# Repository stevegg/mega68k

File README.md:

# Steve's Mega68k
This project was inspired by others.  It's the unholy union of an Motorola MC68000 CPU and MC68681 DUART with an Arduino Mega along with an AdaFruit SD Card breakout.  This is my attempt to bootstrap building a single board CPU with appropriate software to make it interesting.  My goals are to get the software to a point where it can run both CP/M 68k and a scaled down version of Linux.  

Right now there are 2 software projects:
- Mega68k freerun - implementing a simple freerun mode
- Mega68k simpleLopp - implementing a simple loop and using the arduino as ROM.

Both of these are in the software sub-directory.
The hardware sub-directory contains the KiKad 6.0 project along with the required symbol and footprint libraries and the gerbers.

For Arduino software development I'm using VSCode and the platformio plugin.  This provides a pleasant and smooth development experience.

For assembler I'm using Easy68k...this provides a less smooth and pleasant development experience but it does work and the simulation is quite useful.

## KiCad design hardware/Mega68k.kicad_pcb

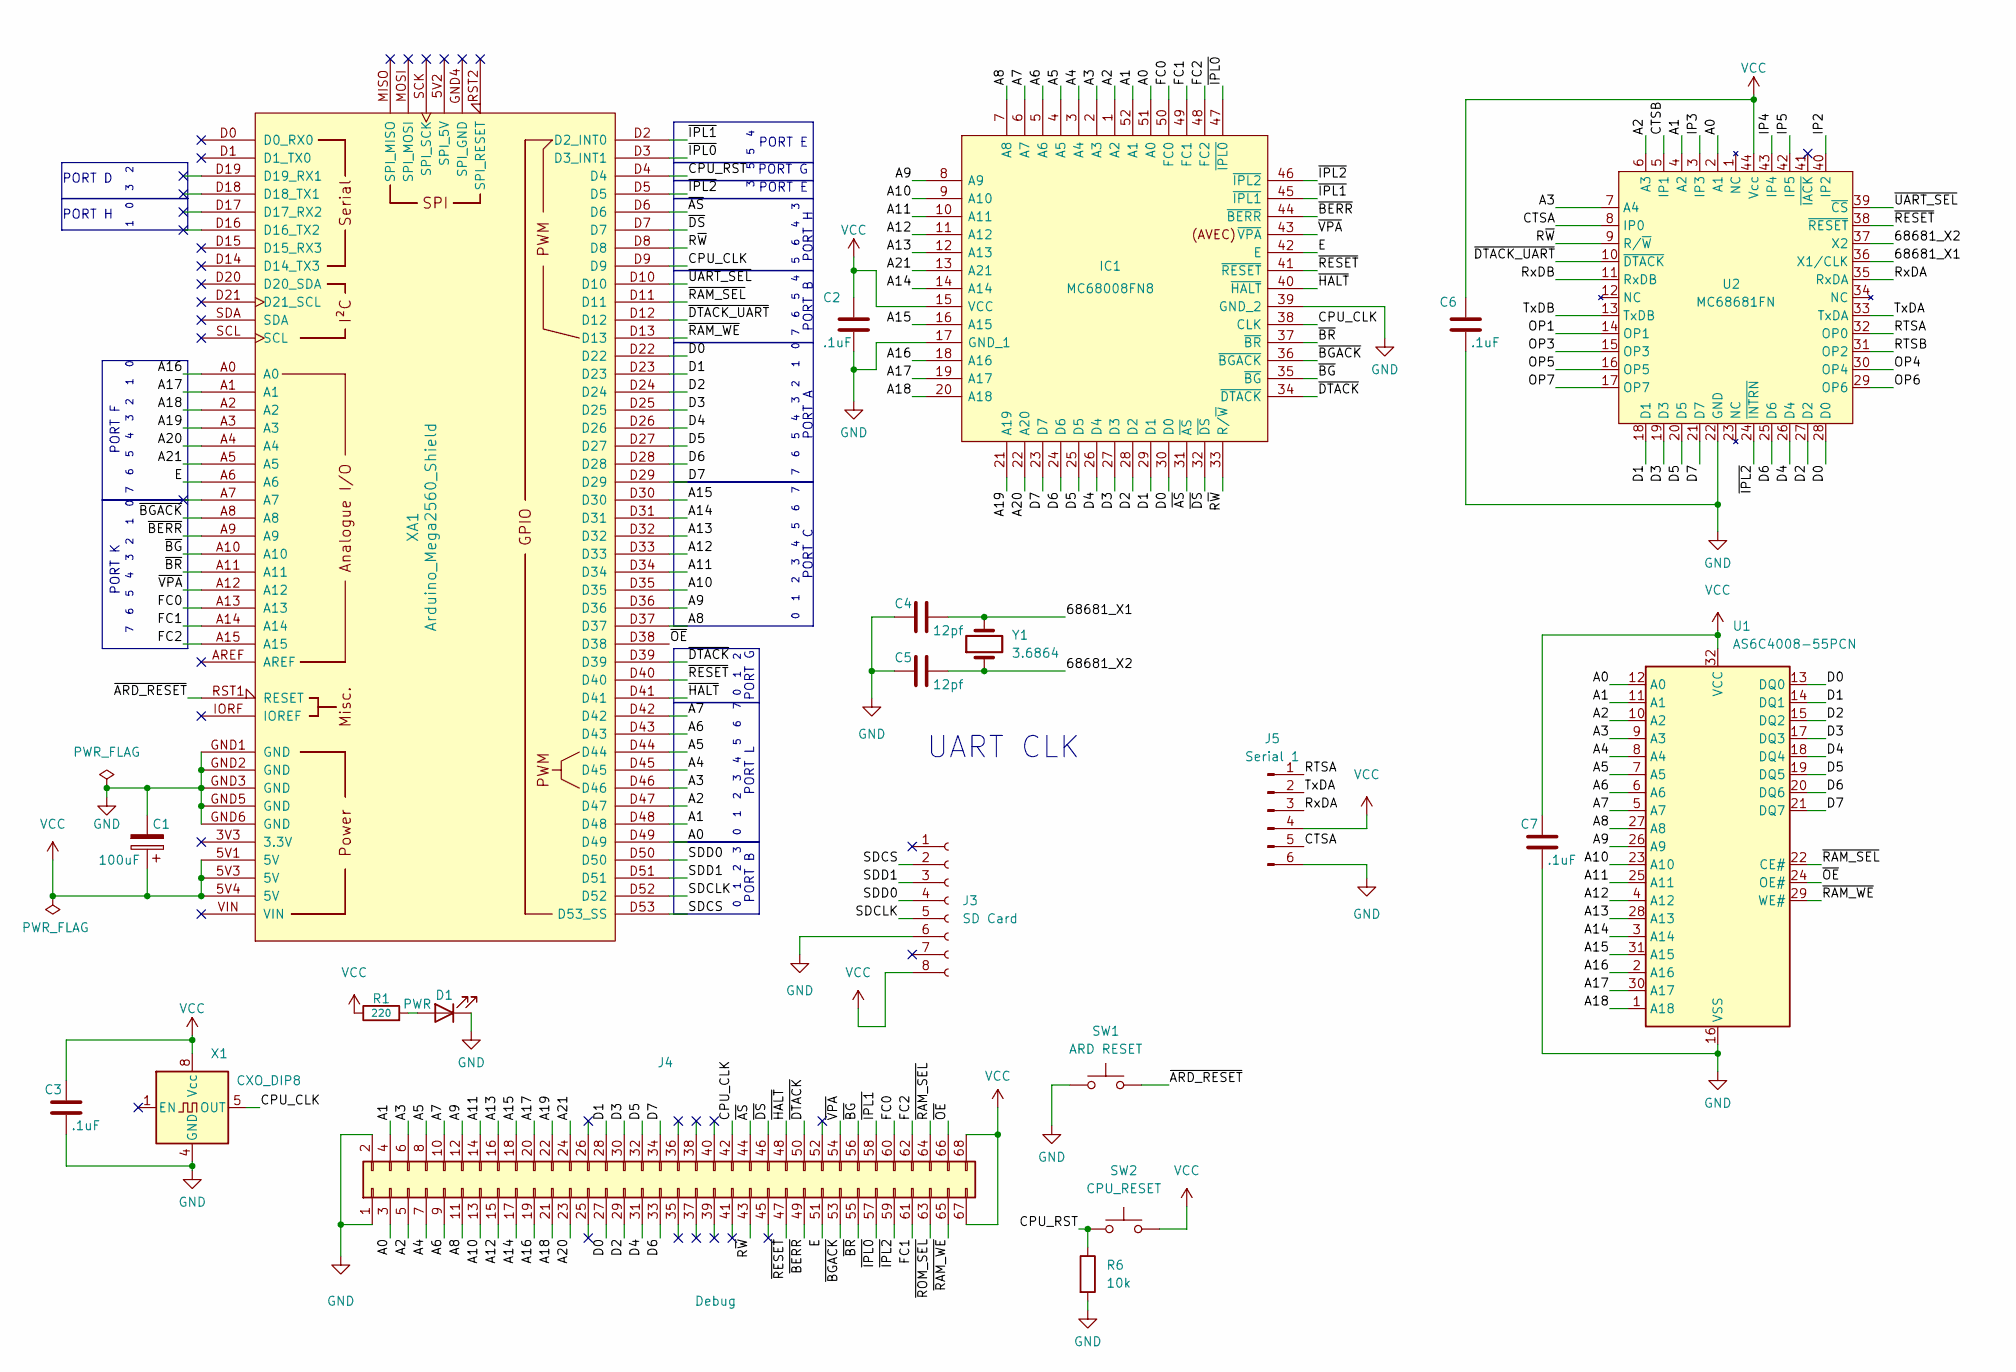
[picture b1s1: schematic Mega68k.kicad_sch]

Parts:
C1: 100uF; CP_Elec_4x5.4
C2, C3, C6, C7: .1uF; C_0603_1608Metric
C4, C5: 12pf; C_0603_1608Metric
D1: PWR; LED_1206_3216Metric
IC1: MC68008FN8; PLCC-52_THT-Socket; Manufacturer_Part_Number MC68008FN8
J3: SD Card; PinSocket_1x08_P2.54mm_Vertical
J4: Debug; PinHeader_2x34_P2.54mm_Vertical
J5: Serial 1; PinHeader_1x06_P2.54mm_Vertical
R1: 220; R_0603_1608Metric
R6: 10k; R_0603_1608Metric
SW1: ARD RESET; SW_PUSH_6mm
SW2: CPU_RESET; SW_PUSH_6mm
U1: AS6C4008-55PCN; SSOP-32_11.305x20.495mm_P1.27mm
U2: MC68681FN; PLCC-44_THT-Socket
X1: CXO_DIP8; Oscillator_DIP-8
XA1: Arduino_Mega2560_Shield
Y1: 3.6864; Crystal_HC49-U_Vertical

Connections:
/68681_X1: C4.2, U2.36 (X1/CLK), Y1.2
/68681_X2: C5.2, U2.37 (X2), Y1.1
/A0: IC1.51 (A0), J4.3, U1.12 (A0), U2.2 (A1), XA1.D49
/A1: IC1.52 (A1), J4.4, U1.11 (A1), U2.4 (A2), XA1.D48
/A2: IC1.1 (A2), J4.5, U1.10 (A2), U2.6 (A3), XA1.D47
/A3: IC1.2 (A3), J4.6, U1.9 (A3), U2.7 (A4), XA1.D46
/A4: IC1.3 (A4), J4.7, U1.8 (A4), XA1.D45
/A5: IC1.4 (A5), J4.8, U1.7 (A5), XA1.D44
/A6: IC1.5 (A6), J4.9, U1.6 (A6), XA1.D43
/A7: IC1.6 (A7), J4.10, U1.5 (A7), XA1.D42
/A8: IC1.7 (A8), J4.11, U1.27 (A8), XA1.D37
/A9: IC1.8 (A9), J4.12, U1.26 (A9), XA1.D36
/A10: IC1.9 (A10), J4.13, U1.23 (A10), XA1.D35
/A11: IC1.10 (A11), J4.14, U1.25 (A11), XA1.D34
/A12: IC1.11 (A12), J4.15, U1.4 (A12), XA1.D33
/A13: IC1.12 (A13), J4.16, U1.28 (A13), XA1.D32
/A14: IC1.14 (A14), J4.17, U1.3 (A14), XA1.D31
/A15: IC1.16 (A15), J4.18, U1.31 (A15), XA1.D30
/A16: IC1.18 (A16), J4.19, U1.2 (A16), XA1.A0
/A17: IC1.19 (A17), J4.20, U1.30 (A17), XA1.A1
/A18: IC1.20 (A18), J4.21, U1.1 (A18), XA1.A2
/A19: IC1.21 (A19), J4.22, XA1.A3
/A20: IC1.22 (A20), J4.23, XA1.A4
/A21: IC1.13 (A21), J4.24, XA1.A5
/CPU_CLK: IC1.38 (CLK), J4.42, X1.5 (OUT), XA1.D9
/CPU_RST: R6.1, SW2.1, XA1.D4
/CTSA: J5.5, U2.8 (IP0)
/CTSB: U2.5 (IP1)
/D0: IC1.30 (D0), J4.27, U1.13 (DQ0), U2.28 (D0), XA1.D22
/D1: IC1.29 (D1), J4.28, U1.14 (DQ1), U2.18 (D1), XA1.D23
/D2: IC1.28 (D2), J4.29, U1.15 (DQ2), U2.27 (D2), XA1.D24
/D3: IC1.27 (D3), J4.30, U1.17 (DQ3), U2.19 (D3), XA1.D25
/D4: IC1.26 (D4), J4.31, U1.18 (DQ4), U2.26 (D4), XA1.D26
/D5: IC1.25 (D5), J4.32, U1.19 (DQ5), U2.20 (D5), XA1.D27
/D6: IC1.24 (D6), J4.33, U1.20 (DQ6), U2.25 (D6), XA1.D28
/D7: IC1.23 (D7), J4.34, U1.21 (DQ7), U2.21 (D7), XA1.D29
/E: IC1.42 (E), J4.51, XA1.A6
/FC0: IC1.50 (FC0), J4.60, XA1.A13
/FC1: IC1.49 (FC1), J4.61, XA1.A14
/FC2: IC1.48 (FC2), J4.62, XA1.A15
/IP2: U2.40 (IP2)
/IP3: U2.3 (IP3)
/IP4: U2.43 (IP4)
/IP5: U2.42 (IP5)
/OP1: U2.14 (OP1)
/OP3: U2.15 (OP3)
/OP4: U2.30 (OP4)
/OP5: U2.16 (OP5)
/OP6: U2.29 (OP6)
/OP7: U2.17 (OP7)
/RTSA: J5.1, U2.32 (OP0)
/RTSB: U2.31 (OP2)
/RxDA: J5.3, U2.35 (RxDA)
/RxDB: U2.11 (RxDB)
/R~W: IC1.33 (R/~W), J4.43, U2.9 (R/~W), XA1.D8
/SDCLK: J3.5, XA1.D52
/SDCS: J3.2, XA1.D53 (D53_SS)
/SDD0: J3.4, XA1.D50
/SDD1: J3.3, XA1.D51
/TxDA: J5.2, U2.33 (TxDA)
/TxDB: U2.13 (TxDB)
/~ARD_RESET: SW1.2, XA1.RST1 (RESET)
/~AS: IC1.31 (~AS), J4.44, XA1.D6
/~BERR: IC1.44 (~BERR), J4.49, XA1.A9
/~BGACK: IC1.36 (~BGACK), J4.53, XA1.A8
/~BG: IC1.35 (~BG), J4.56, XA1.A10
/~BR: IC1.37 (~BR), J4.55, XA1.A11
/~DS: IC1.32 (~DS), J4.46, XA1.D7
/~DTACK_UART: U2.10 (~DTACK), XA1.D12
/~DTACK: IC1.34 (~DTACK), J4.50, XA1.D39
/~HALT: IC1.40 (~HALT), J4.48, XA1.D41
/~IPL0: IC1.47 (~IPL0), J4.57, XA1.D3 (D3_INT1)
/~IPL1: IC1.45 (~IPL1), J4.58, XA1.D2 (D2_INT0)
/~IPL2: IC1.46 (~IPL2), J4.59, U2.24 (~INTRN), XA1.D5
/~OE: J4.66, U1.24 (OE#), XA1.D38
/~RAM_SEL: J4.64, U1.22 (CE#), XA1.D11
/~RAM_WE: J4.65, U1.29 (WE#), XA1.D13
/~RESET: IC1.41 (~RESET), J4.47, U2.38 (~RESET), XA1.D40
/~ROM_SEL: J4.63
/~UART_SEL: U2.39 (~CS), XA1.D10
/~VPA: IC1.43 (~VPA), J4.54, XA1.A12
GND: C1.2, C2.2, C3.2, C4.1, C5.1, C6.2, C7.2, D1.1 (K), IC1.17 (GND_1), IC1.39 (GND_2), J3.6, J4.1, J4.2, J5.6, R6.2, SW1.1, U1.16 (VSS), U2.22 (GND), X1.4 (GND), XA1.GND1 (GND), XA1.GND2 (GND), XA1.GND3 (GND), XA1.GND5 (GND), XA1.GND6 (GND)
unnamed: D1.2 (A), R1.2
VCC: C1.1, C2.1, C3.1, C6.1, C7.1, IC1.15 (VCC), J3.8, J4.67, J4.68, J5.4, R1.1, SW2.2, U1.32 (VCC), U2.44 (Vcc), X1.8 (Vcc), XA1.5V1 (5V), XA1.5V3 (5V), XA1.5V4 (5V)

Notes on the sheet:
PORT H
PORT A
UART CLK
PORT E
PORT B
PORT D
PORT C
PORT G
PORT K
PORT F
PORT L

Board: 2 copper layers, 23 parts (2 on the bottom side), 69 nets, no tracks yet.

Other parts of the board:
Logo1: KiCad-Logo2_8mm_SilkScreen
Logo2: OSHW-Logo2_9.8x8mm_SilkScreen

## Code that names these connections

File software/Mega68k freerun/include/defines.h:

#ifndef __DEFINES_H
#define __DEFINES_H

#include <Arduino.h>

// Low byte of address bus
#define ADDRESS_LOW_PIN     PINL
#define ADDRESS_LOW_PORT    PORTL
#define ADDRESS_LOW_DDR     DDRL

// Hi byte of address bus
#define ADDRESS_HI_PIN      PINC
#define ADDRESS_HI_PORT     PORTC
#define ADDRESS_HI_DDR      DDRC

// Extra byte of address bus
#define ADDRESS_X_PIN       PINB
#define ADDRESS_X_PORT      PORTB
#define ADDRESS_X_DDR       DDRB

// Low byte of data bus
#define DATA_LOW_PIN        PINA
#define DATA_LOW_PORT       PORTA
#define DATA_LOW_DDR        DDRA

// Hi byte of data bus
#define DATA_HI_PIN         PINF
#define DATA_HI_PORT        PORTF
#define DATA_HI_DDR         DDRF

#define ADDRESS_STROBE_PIN  PORTD1
#define READ_WRITE          7
#define READ_WRITE_PIN      PORTH4

#define DTACK_PORT          PORTG2
#define DTACK_PIN           PING2
#define RESET_PORT          PORTG1
#define RESET_PIN           PING1
#define HALT_PORT           PORTG0
#define HALT_PIN            PING0

#define RW_PIN              PORTH4
#define CLK_INPUT           PORTG5

#define VPA_PIN             PORTK4
#define BERR_PIN            PORTK1
#define BGACK_PIN           PORTK0
#define BR_PIN              PORTK3

#define IPL0_PIN            PORTE5
#define IPL1_PIN            PORTE4
#define IPL2_PIN            PORTE3

#define FC0_PIN             PORTH0
#define FC1_PIN             PORTH1
#define FC2_PIN             PORTH3

#define CHECK_BIT(var,pos) ((var) & (1<<(pos)))

#define IsReading()         (PORTH & (1<<PORTH4)) > 0

#endif

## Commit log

2022-07-21 Initial commit of V220718
2022-08-04 Fixed 64 pin socket size and added more status lights
2022-08-04 Updated version label
2022-08-06 Updated with trace routing
2022-08-06 Added an arduino reset switch
2022-08-06 Added freerun software sketch for platformio
2022-08-11 Working freerun
2022-08-11 Cleanup of freerun code
2022-08-11 More cleanup
2022-08-12 More tweaks to schematics before next rev V20220811
2022-08-12 Added simple loop code and finalized board
2022-08-14 Added program to do simple loop testing ROM access
2022-08-14 Some code cleanup
2022-08-14 Some Reorganization
2022-08-14 Some cleanup
2022-08-14 Added PCB image for V20220811
2022-08-14 Tweaks to readme and some cleanup
2022-08-20 Updated Mega68k freerun sketch to work with rev V20220811
